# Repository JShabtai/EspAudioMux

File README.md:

# Intro

This project uses an ESP8266 and a 74HC4052 to control 4 stereo audio channels.

# Build/flash

## Requirements

The following tools are required and must be available on your PATH

* nodemcu-tool
* esptool

To run this on your ESP8266, flash the NodeMcu firmware that is pre-compiled and available in this repo.
To do this you must first put the ESP8266 into flashing mode. To do this, hold the flashing button on your
module (which is connected to GPIO0) and press the reset button. Then run the following:

```
make flash
```

Once that's done successfully, you need to upload the lua files:

```
make upload
```

# How to use

When the module boots up it will attempt to connect to a WiFi network if it already knows about one. If that fails,
then it will automatically enter WPS mode. Simply press the WPS button on your router then restart the ESP8266.
The EPS8266 will get the Wi-Fi credentials and connect automatically. This only needs to be done once - the
credentials are remembered.

You will need to know the IP of your device to connect to it. When the device connects to a Wi-Fi network it will
print out its IP address. Use the following command to restart the device (forcing it to re-connect)

```
make restart terminal
```

You will see a line something like this:

```
Connected to WIFI with IP: 192.168.0.101
```

It is recommended that you add a DHCP reservation on your router to keep the IP from changing, so you don't need to
repeat these steps. If your router supports this, then consult your routers documentation for instructions.

By default the MUX is off, and channel 0 is selected.

## API

The module exposes a few simple endpoints to control the MUX:

* `/enable`: Turn the MUX on.
* `/disable`: Turn the MUX off.
* `/channel/x`: Select channel `x`, where `x` is between 0 and 3 inclusive

# Future improvements

* Add LEDs to indicate which channel is active or if the device is off
* Add physical button to switch the channel manually
* Remember MUX status (on/of and channel)

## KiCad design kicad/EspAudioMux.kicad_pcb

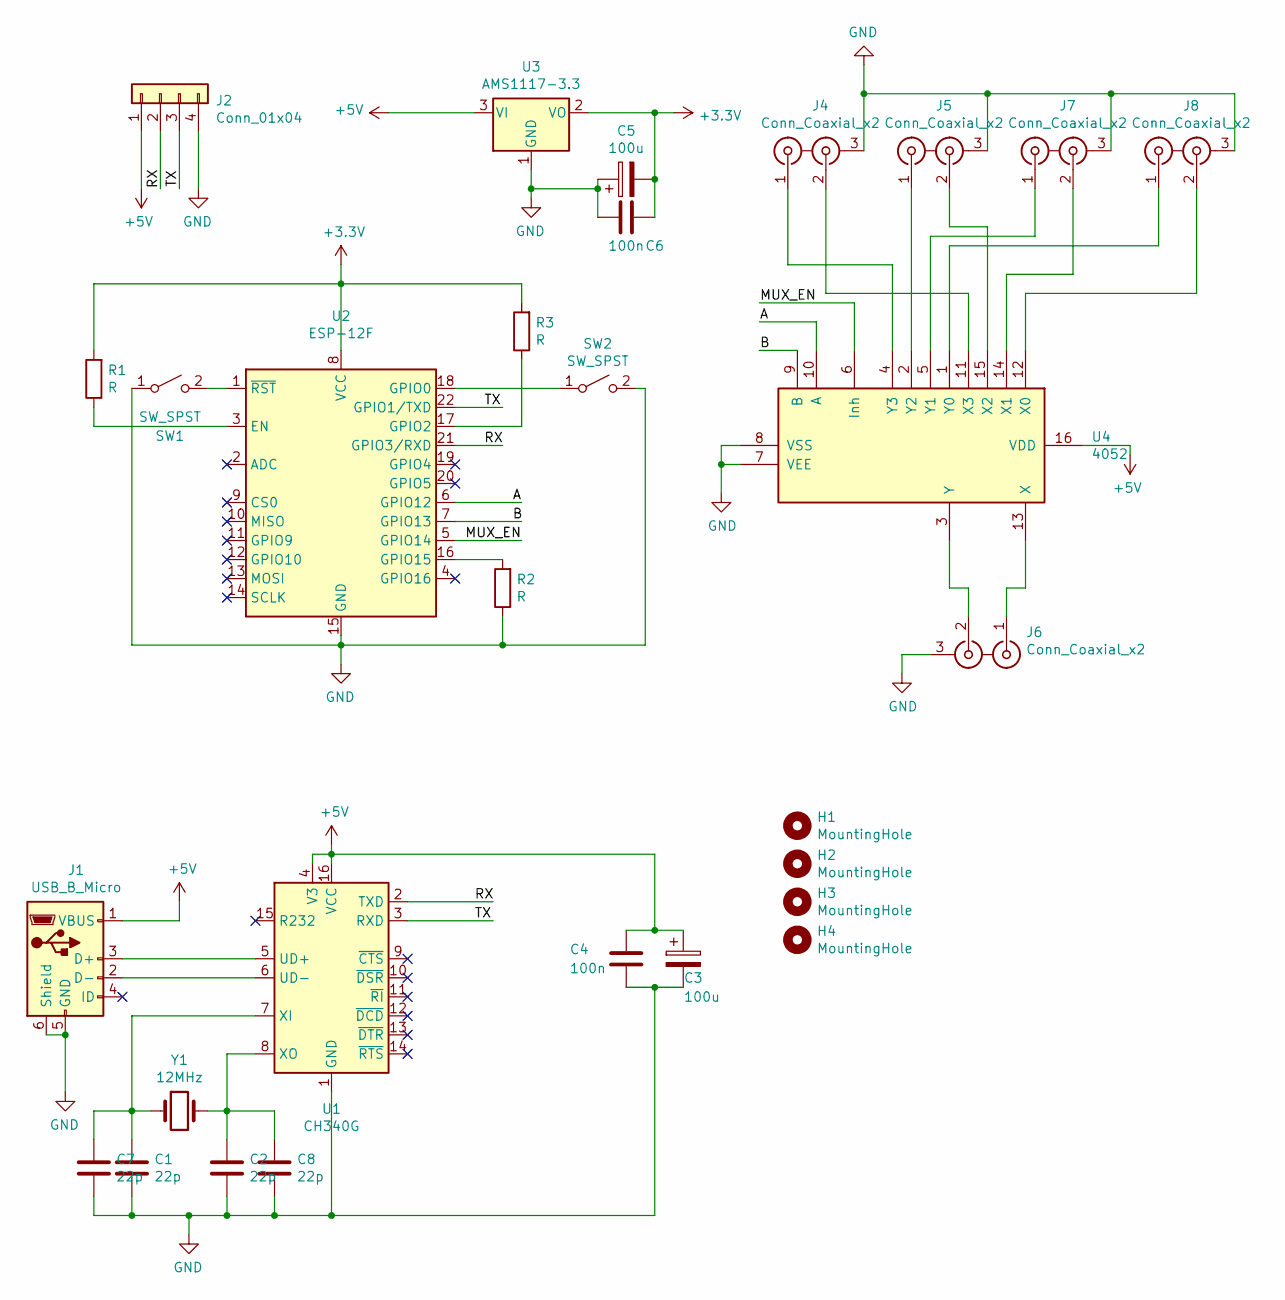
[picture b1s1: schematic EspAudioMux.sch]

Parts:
C1, C2: 22p; C_0603_1608Metric_Pad1.05x0.95mm_HandSolder
C3, C5: 100u; CP_Radial_D8.0mm_P2.50mm
C4, C6: 100n; C_0603_1608Metric_Pad1.05x0.95mm_HandSolder
C7, C8: 22p; C_Disc_D3.0mm_W1.6mm_P2.50mm
H1, H2, H3, H4: MountingHole; MountingHole_2.2mm_M2
J1: USB_B_Micro; USB_Micro-B_Wuerth_629105150521_CircularHoles
J2: Conn_01x04; PinHeader_1x04_P2.54mm_Vertical
J4, J5, J6, J7, J8: Conn_Coaxial_x2; RCA_3.5mm
R1, R2, R3: R; R_0603_1608Metric_Pad1.05x0.95mm_HandSolder
SW1, SW2: SW_SPST; SW_SPST_EVQP0
U1: CH340G; SOIC-16_3.9x9.9mm_P1.27mm
U2: ESP-12F; ESP-12E
U3: AMS1117-3.3; SOT-223-3_TabPin2
U4: 4052; DIP-16_W7.62mm_Socket_LongPads
Y1: 12MHz; Crystal_HC18-U_Vertical

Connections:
+3V3: C5.2, C6.1, R1.2, R3.2, U2.8 (VCC), U3.2 (VO)
+5V: C3.1, C4.2, J1.1 (VBUS), J2.1, U1.4 (V3), U1.16 (VCC), U3.3 (VI), U4.16 (VDD)
/A: U2.6 (GPIO12), U4.10 (A)
/B: U2.7 (GPIO13), U4.9 (B)
/MUX_EN: U2.5 (GPIO14), U4.6 (Inh)
/RX: J2.2, U1.2 (TXD), U2.21 (GPIO3/RXD)
/TX: J2.3, U1.3 (RXD), U2.22 (GPIO1/TXD)
GND: C1.2, C2.2, C3.2, C4.1, C5.1, C6.2, C7.2, C8.2, J1.5 (GND), J1.6 (Shield), J2.4, J4.3 (EXT), J5.3 (EXT), J6.3 (EXT), J7.3 (EXT), J8.3 (EXT), R2.1, SW1.1 (A), SW2.2 (B), U1.1 (GND), U2.15 (GND), U3.1 (GND), U4.7 (VEE), U4.8 (VSS)
unnamed: C1.1, C7.1, U1.7 (XI), Y1.1
unnamed: C2.1, C8.1, U1.8 (XO), Y1.2
unnamed: J1.2 (D-), U1.6 (UD-)
unnamed: J1.3 (D+), U1.5 (UD+)
unnamed: J4.1 (IN1), U4.4 (Y3)
unnamed: J4.2 (IN2), U4.11 (X3)
unnamed: J5.1 (IN1), U4.2 (Y2)
unnamed: J5.2 (IN2), U4.15 (X2)
unnamed: J6.1 (IN1), U4.13 (X)
unnamed: J6.2 (IN2), U4.3 (Y)
unnamed: J7.1 (IN1), U4.5 (Y1)
unnamed: J7.2 (IN2), U4.14 (X1)
unnamed: J8.1 (IN1), U4.1 (Y0)
unnamed: J8.2 (IN2), U4.12 (X0)
unnamed: R1.1, U2.3 (EN)
unnamed: R2.2, U2.16 (GPIO15)
unnamed: R3.1, U2.17 (GPIO2)
unnamed: SW1.2 (B), U2.1 (~RST)
unnamed: SW2.1 (A), U2.18 (GPIO0)

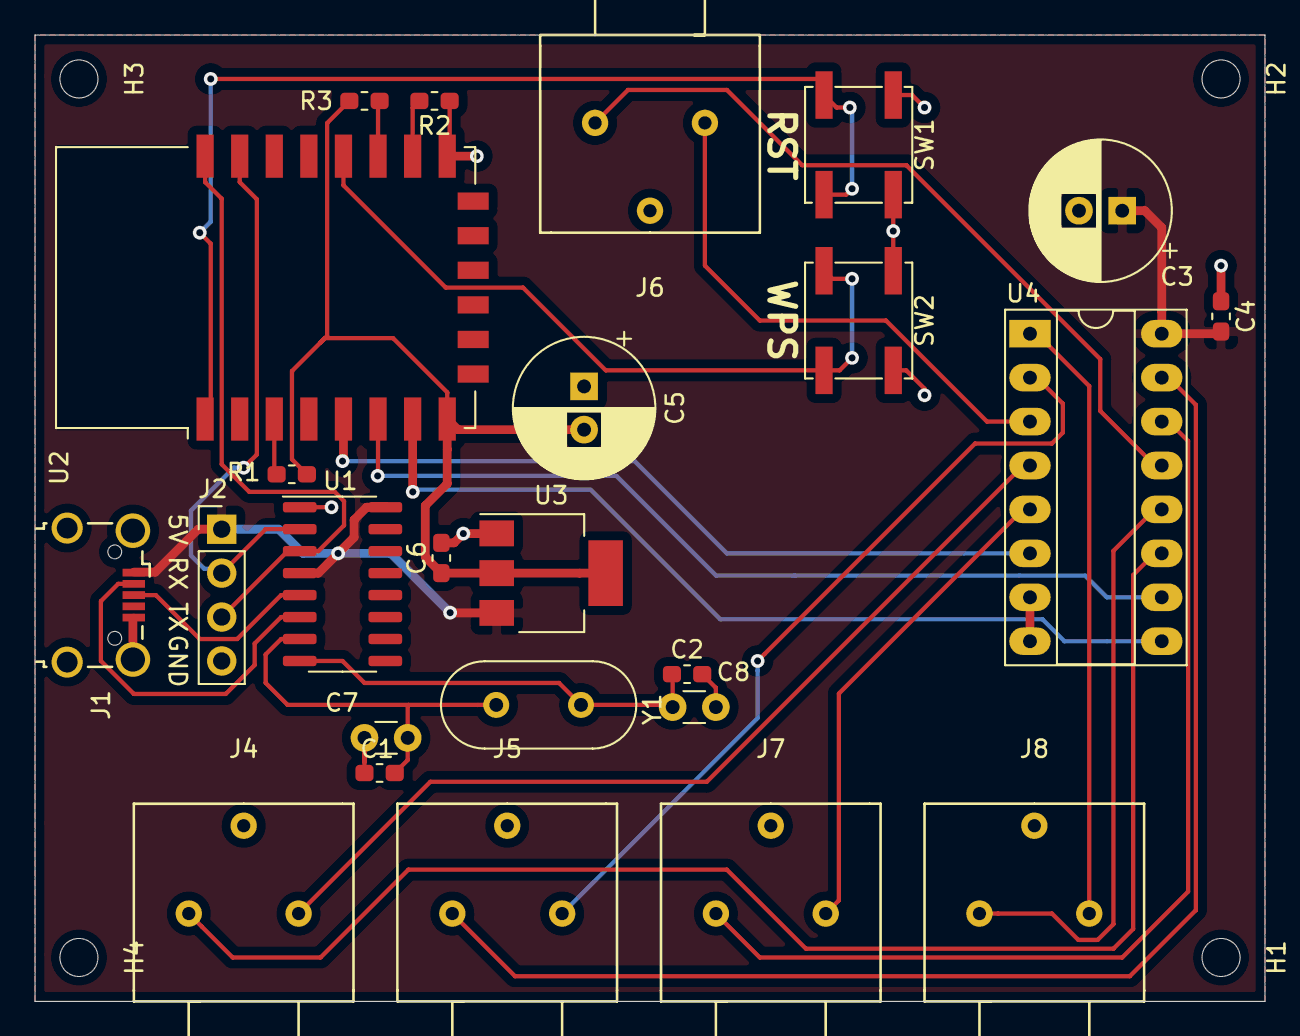
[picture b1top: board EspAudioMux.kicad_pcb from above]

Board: 2 copper layers, 71.1 x 55.9 mm, 29 parts (0 on the bottom side), 27 nets.

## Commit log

2019-04-15 Initial commit:
    * Basic build scripts
    * NodeMcu firmware
    * Working MUX code
2019-05-13 Added v0.1 circuit (schematic and PCB)
    * Will probably redo layout alltogether

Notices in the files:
kicad/EspAudioMux.kicad_pcb:
License: TODO
